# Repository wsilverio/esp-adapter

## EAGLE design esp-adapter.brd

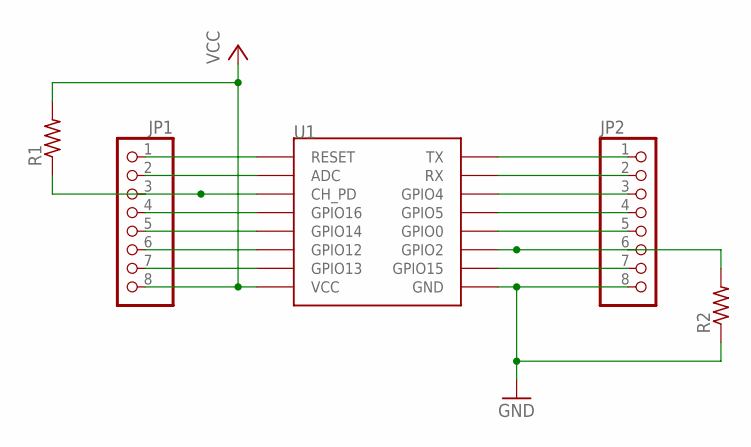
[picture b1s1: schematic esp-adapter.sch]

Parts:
JP1, JP2: PINHD-1X8; 1X08
R1, R2: R-US_R0805; R0805
U1: ESP12SMD; ESP12-SMD

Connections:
GND: JP2.8, R2.1, U1.GND
unnamed: JP1.1, U1.RESET
unnamed: JP1.2, U1.ADC
unnamed: JP1.3, R1.1, U1.CH_PD
unnamed: JP1.4, U1.GPIO16
unnamed: JP1.5, U1.GPIO14
unnamed: JP1.6, U1.GPIO12
unnamed: JP1.7, U1.GPIO13
unnamed: JP2.1, U1.TXD0 (TX)
unnamed: JP2.2, U1.RXD0 (RX)
unnamed: JP2.3, U1.GPIO4
unnamed: JP2.4, U1.GPIO5
unnamed: JP2.5, U1.GPIO0
unnamed: JP2.6, R2.2, U1.GPIO2
unnamed: JP2.7, U1.GPIO15
VCC: JP1.8, R1.2, U1.VCC

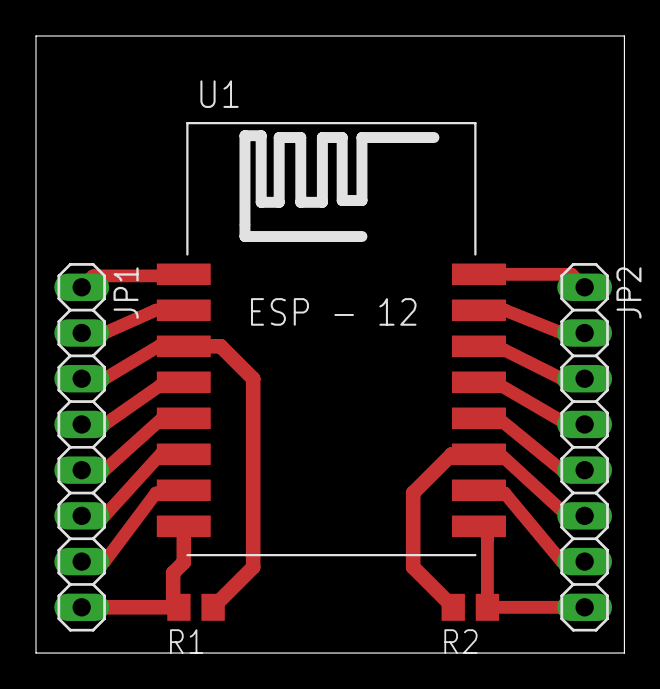
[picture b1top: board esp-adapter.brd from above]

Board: 2 copper layers, 32.7 x 34.3 mm, 5 parts (0 on the bottom side), 16 nets.

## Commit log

2017-05-17 esp adapter v0
